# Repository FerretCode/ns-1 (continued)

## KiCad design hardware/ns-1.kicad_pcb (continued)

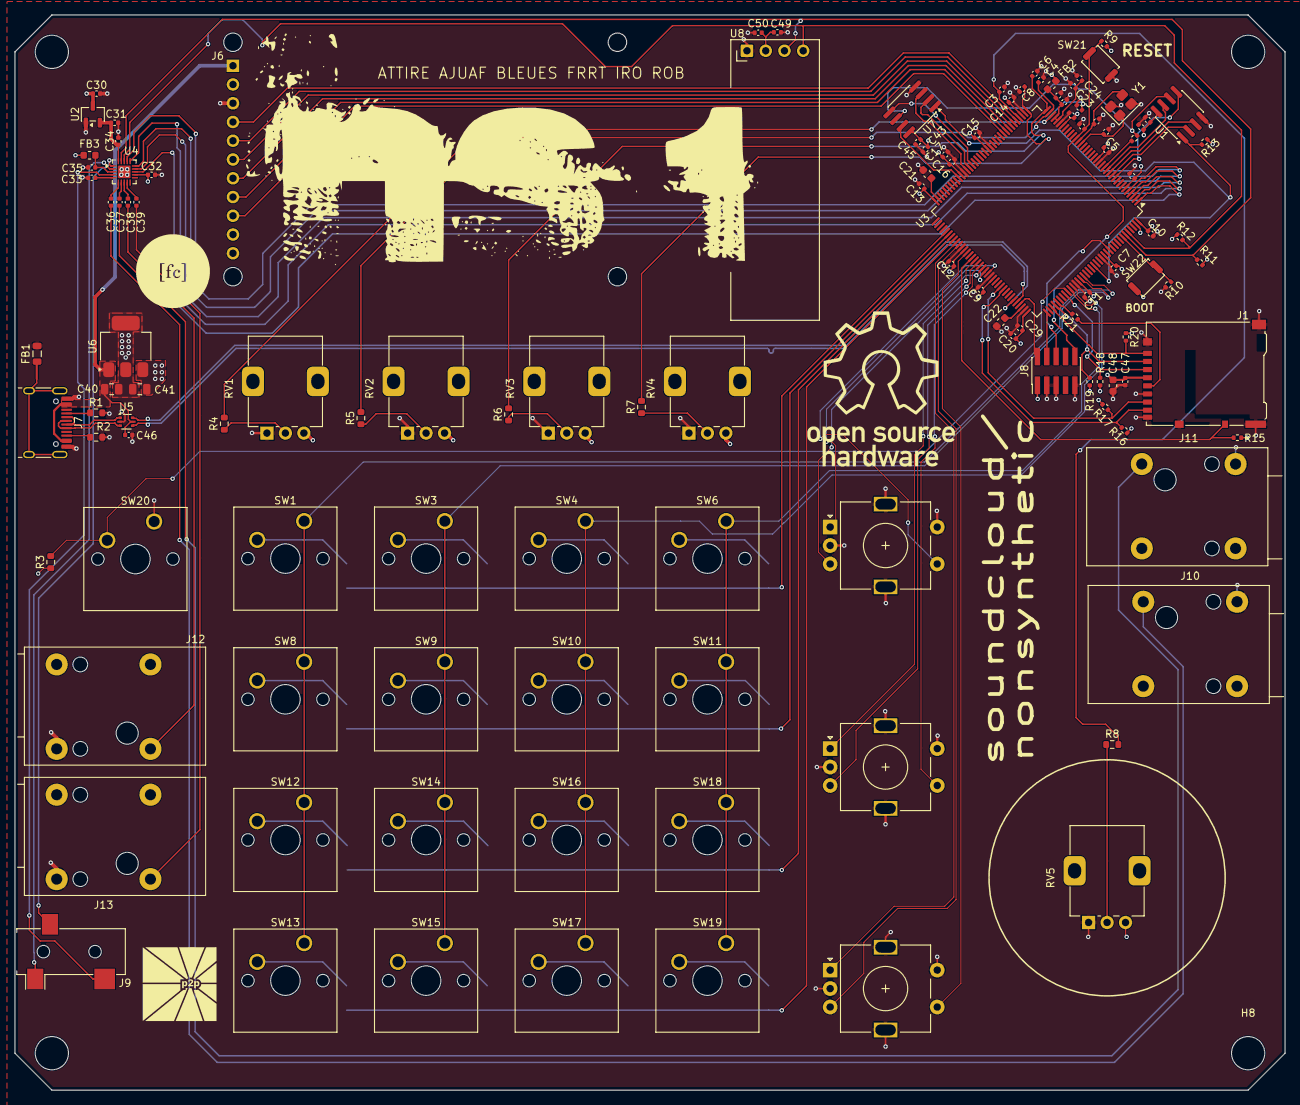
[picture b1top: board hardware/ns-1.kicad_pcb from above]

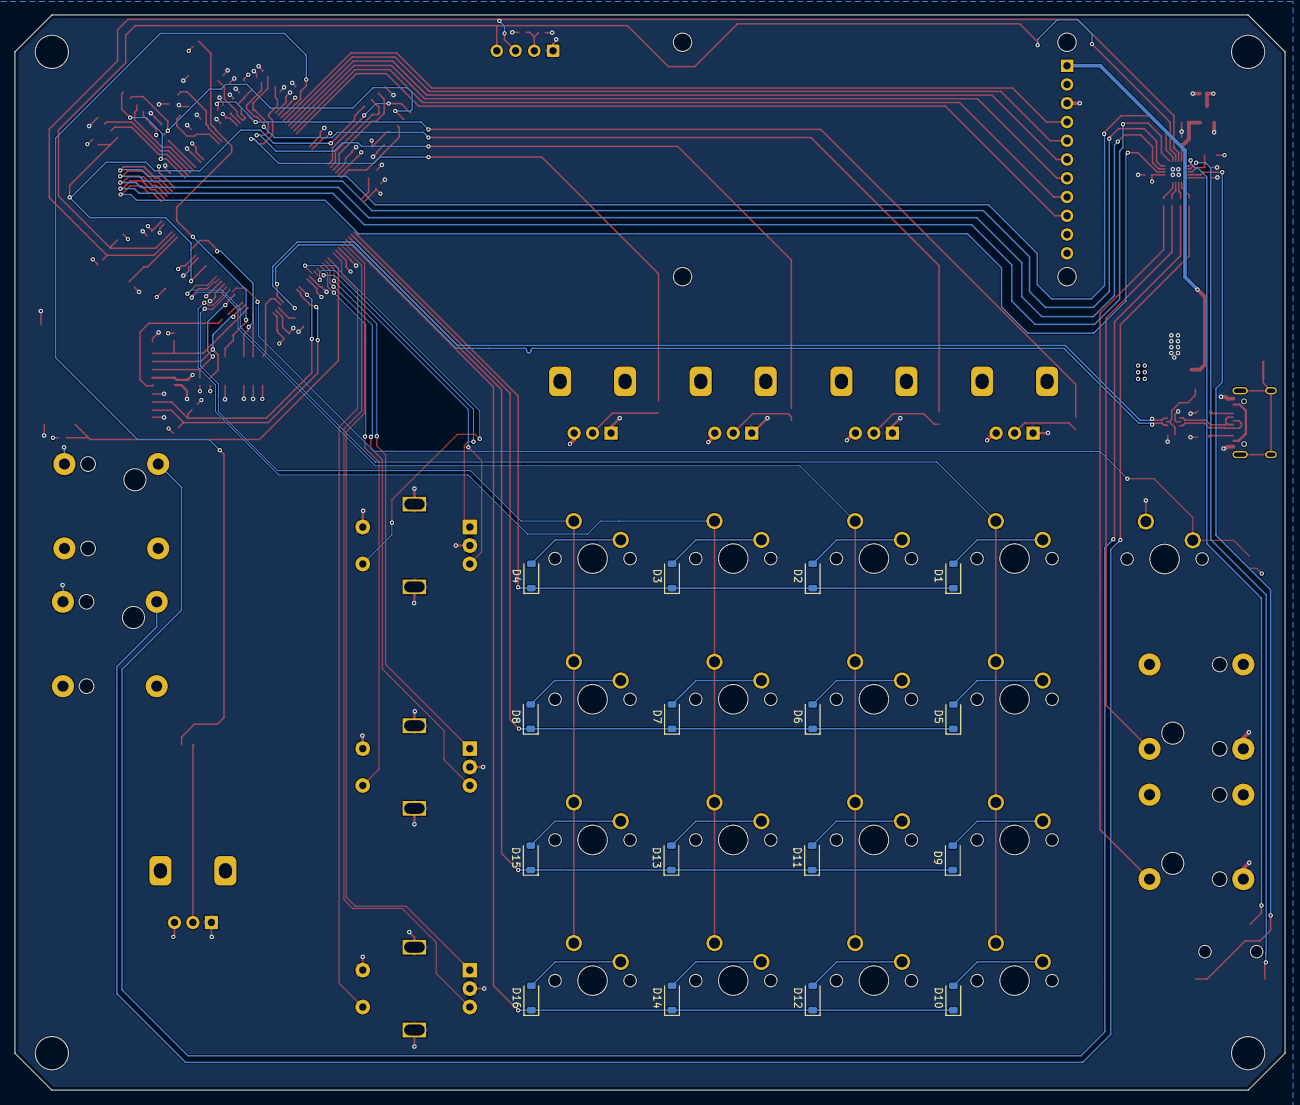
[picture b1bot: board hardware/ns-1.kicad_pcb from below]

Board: 4 copper layers, 172.0 x 145.6 mm, 143 parts (16 on the bottom side), 110 nets.

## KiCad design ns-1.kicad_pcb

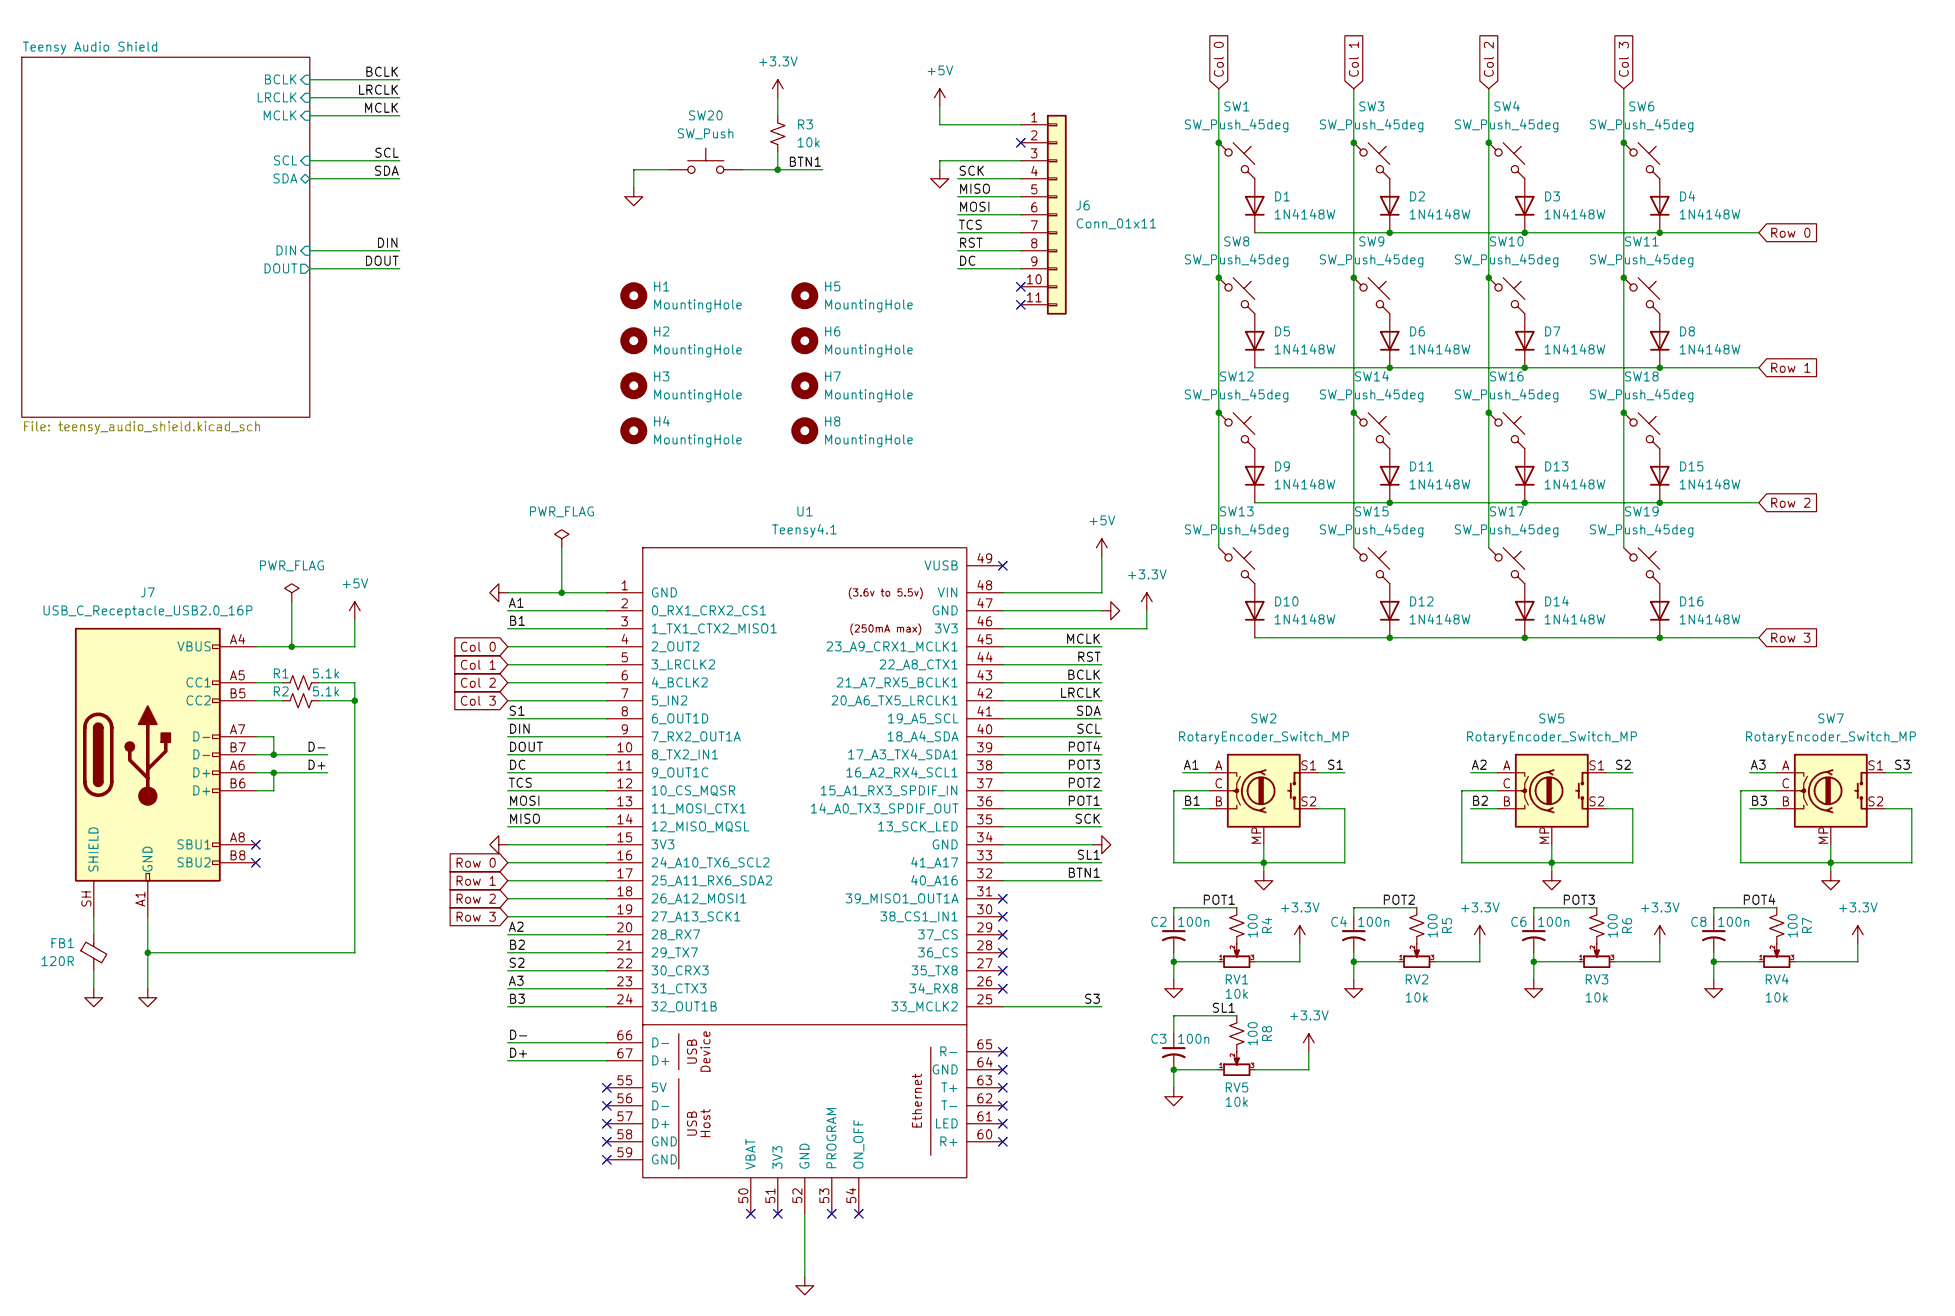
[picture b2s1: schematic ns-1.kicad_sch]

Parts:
C2, C3, C4, C6, C8: 100n; C_0402_1005Metric
D1, D2, D3, D4, D5, D6, D7, D8, D9, D10, D11, D12, D13, D14, D15, D16: 1N4148W; D_SOD-123
FB1: 120R; L_0805_2012Metric
H1, H2, H3, H4: MountingHole; MountingHole_2.5mm
H5, H6, H7, H8: MountingHole; MountingHole_4.5mm
J6: Conn_01x11; PinHeader_1x11_P2.54mm_Vertical
J7: USB_C_Receptacle_USB2.0_16P; USB_C_Receptacle_Amphenol_12401948E412A
R1, R2: 5.1k; R_0603_1608Metric
R3: 10k; R_0603_1608Metric
R4, R5, R6, R7, R8: 100; R_0603_1608Metric
RV1, RV2, RV3, RV4: 10k; Potentiometer_Alps_RK09K_Single_Vertical
RV5: 10k; Potentiometer_Bourns_PTA4543_Single_Slide
SW1, SW3, SW4, SW6, SW8, SW9, SW10, SW11, SW12, SW13, SW14, SW15, SW16, SW17, SW18, SW19: SW_Push_45deg; SW_Cherry_MX_1.00u_PCB
SW2, SW5, SW7: RotaryEncoder_Switch_MP; RotaryEncoder_Alps_EC11E-Switch_Vertical_H20mm
SW20: SW_Push; SW_Cherry_MX_1.00u_PCB
U1: Teensy4.1; Teensy41

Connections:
+3.3V: R3.1, RV1.3, RV2.3, RV3.3, RV4.3, RV5.3, U1.46 (3V3); also elsewhere on the board
+5V: J6.1, J7.A4 (VBUS), J7.A9 (VBUS), J7.B4 (VBUS), J7.B9 (VBUS), U1.48 (VIN)
/A1: SW2.A, U1.2 (0_RX1_CRX2_CS1)
/A2: SW5.A, U1.20 (28_RX7)
/A3: SW7.A, U1.23 (31_CTX3)
/B1: SW2.B, U1.3 (1_TX1_CTX2_MISO1)
/B2: SW5.B, U1.21 (29_TX7)
/B3: SW7.B, U1.24 (32_OUT1B)
/BCLK: U1.43 (21_A7_RX5_BCLK1); also elsewhere on the board
/BTN1: R3.2, SW20.2, U1.32 (40_A16)
/D+: J7.A6 (D+), J7.B6 (D+), U1.67 (D+)
/D-: J7.A7 (D-), J7.B7 (D-), U1.66 (D-)
/DC: J6.9, U1.11 (9_OUT1C)
/DIN: U1.9 (7_RX2_OUT1A); also elsewhere on the board
/DOUT: U1.10 (8_TX2_IN1); also elsewhere on the board
/LRCLK: U1.42 (20_A6_TX5_LRCLK1); also elsewhere on the board
/MCLK: U1.45 (23_A9_CRX1_MCLK1); also elsewhere on the board
/MISO: J6.5, U1.14 (12_MISO_MQSL)
/MOSI: J6.6, U1.13 (11_MOSI_CTX1)
/POT1: C2.1, R4.2, U1.36 (14_A0_TX3_SPDIF_OUT)
/POT2: C4.1, R5.2, U1.37 (15_A1_RX3_SPDIF_IN)
/POT3: C6.1, R6.2, U1.38 (16_A2_RX4_SCL1)
/POT4: C8.1, R7.2, U1.39 (17_A3_TX4_SDA1)
/RST: J6.8, U1.44 (22_A8_CTX1)
/S1: SW2.S1, U1.8 (6_OUT1D)
/S2: SW5.S1, U1.22 (30_CRX3)
/S3: SW7.S1, U1.25 (33_MCLK2)
/SCK: J6.4, U1.35 (13_SCK_LED)
/SCL: U1.40 (18_A4_SDA); also elsewhere on the board
/SDA: U1.41 (19_A5_SCL); also elsewhere on the board
/SL1: C3.1, R8.2, U1.33 (41_A17)
/TCS: J6.7, U1.12 (10_CS_MQSR)
Col 0: SW1.1, SW8.1, SW12.1, SW13.1, U1.4 (2_OUT2)
Col 1: SW3.1, SW9.1, SW14.1, SW15.1, U1.5 (3_LRCLK2)
Col 2: SW4.1, SW10.1, SW16.1, SW17.1, U1.6 (4_BCLK2)
Col 3: SW6.1, SW11.1, SW18.1, SW19.1, U1.7 (5_IN2)
GND: C2.2, C3.2, C4.2, C6.2, C8.2, FB1.2, J6.3, J7.A1 (GND), J7.A12 (GND), J7.B1 (GND), J7.B12 (GND), R1.2, R2.2, RV1.1, RV2.1, RV3.1, RV4.1, RV5.1, SW2.C, SW2.MP, SW2.S2, SW5.C, SW5.MP, SW5.S2, SW7.C, SW7.MP, SW7.S2, SW20.1, U1.1 (GND), U1.15 (3V3), U1.34 (GND), U1.47 (GND), U1.52 (GND); also elsewhere on the board
unnamed: D1.2 (A), SW1.2
unnamed: D2.2 (A), SW3.2
unnamed: D3.2 (A), SW4.2
unnamed: D4.2 (A), SW6.2
unnamed: D5.2 (A), SW8.2
unnamed: D6.2 (A), SW9.2
unnamed: D7.2 (A), SW10.2
unnamed: D8.2 (A), SW11.2
unnamed: D9.2 (A), SW12.2
unnamed: D10.2 (A), SW13.2
unnamed: D11.2 (A), SW14.2
unnamed: D12.2 (A), SW15.2
unnamed: D13.2 (A), SW16.2
unnamed: D14.2 (A), SW17.2
unnamed: D15.2 (A), SW18.2
unnamed: D16.2 (A), SW19.2
unnamed: J7.A5 (CC1), R1.1
unnamed: J7.B5 (CC2), R2.1
unnamed: FB1.1, J7.SH (SHIELD)
unnamed: R4.1, RV1.2
unnamed: R5.1, RV2.2
unnamed: R6.1, RV3.2
unnamed: R7.1, RV4.2
unnamed: R8.1, RV5.2
Row 0: D1.1 (K), D2.1 (K), D3.1 (K), D4.1 (K), U1.16 (24_A10_TX6_SCL2)
Row 1: D5.1 (K), D6.1 (K), D7.1 (K), D8.1 (K), U1.17 (25_A11_RX6_SDA2)
Row 2: D9.1 (K), D11.1 (K), D13.1 (K), D15.1 (K), U1.18 (26_A12_MOSI1)
Row 3: D10.1 (K), D12.1 (K), D14.1 (K), D16.1 (K), U1.19 (27_A13_SCK1)

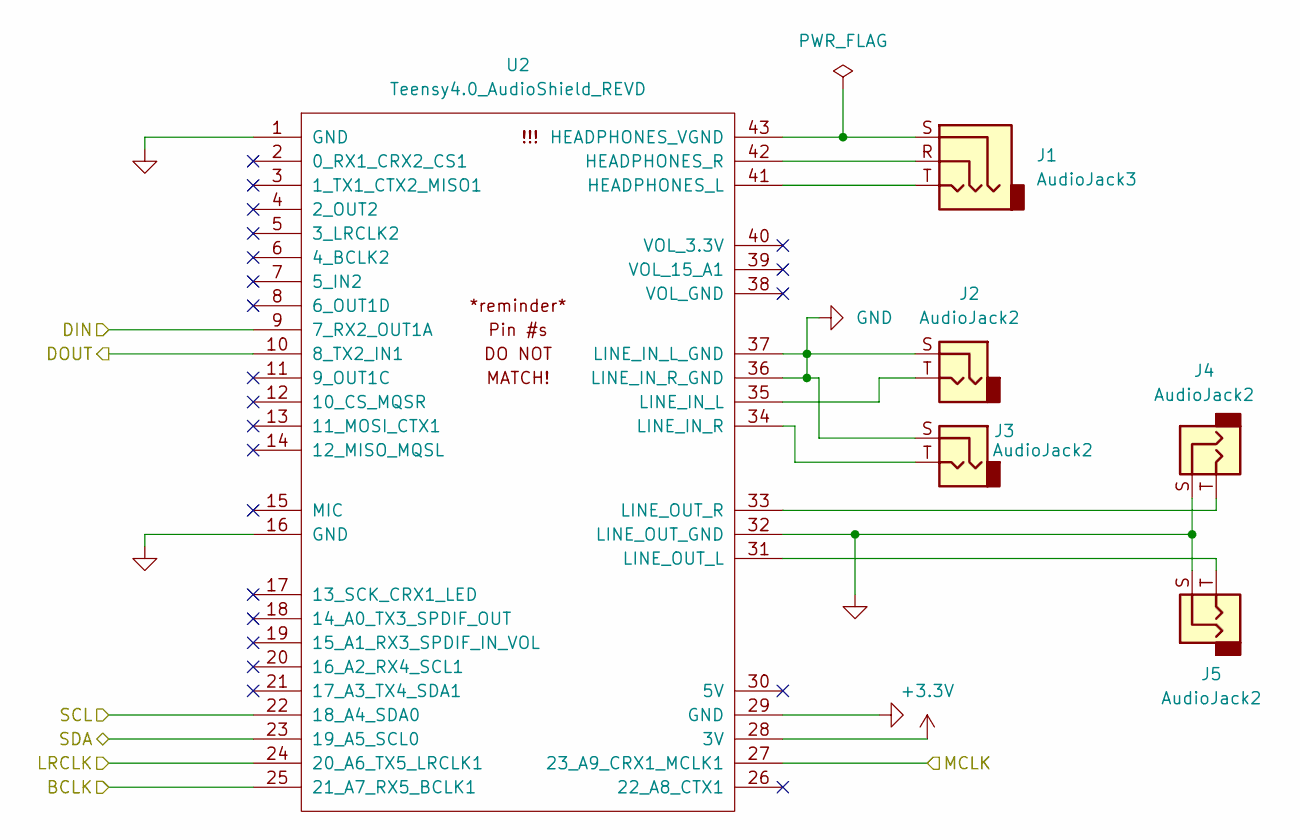
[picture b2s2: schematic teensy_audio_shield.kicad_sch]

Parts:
J1: AudioJack3; Jack_3.5mm_CUI_SJ1-3533NG_Horizontal
J2, J3, J4, J5: AudioJack2; Jack_6.35mm_Neutrik_NRJ4HF_Horizontal
U2: Teensy4.0_AudioShield_REVD; 4.0audioshield

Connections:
+3.3V: U2.28 (3V); also elsewhere on the board
/BCLK: U2.25 (21_A7_RX5_BCLK1); also elsewhere on the board
/DIN: U2.9 (7_RX2_OUT1A); also elsewhere on the board
/DOUT: U2.10 (8_TX2_IN1); also elsewhere on the board
/LRCLK: U2.24 (20_A6_TX5_LRCLK1); also elsewhere on the board
/MCLK: U2.27 (23_A9_CRX1_MCLK1); also elsewhere on the board
/SCL: U2.22 (18_A4_SDA0); also elsewhere on the board
/SDA: U2.23 (19_A5_SCL0); also elsewhere on the board
GND: J2.S, J3.S, J4.S, J5.S, U2.1 (GND), U2.16 (GND), U2.29 (GND), U2.32 (LINE_OUT_GND), U2.36 (LINE_IN_R_GND), U2.37 (LINE_IN_L_GND); also elsewhere on the board
unnamed: J1.T, U2.41 (HEADPHONES_L)
unnamed: J1.R, U2.42 (HEADPHONES_R)
unnamed: J1.S, U2.43 (HEADPHONES_VGND)
unnamed: J2.T, U2.35 (LINE_IN_L)
unnamed: J3.T, U2.34 (LINE_IN_R)
unnamed: J5.T, U2.31 (LINE_OUT_L)
unnamed: J4.T, U2.33 (LINE_OUT_R)

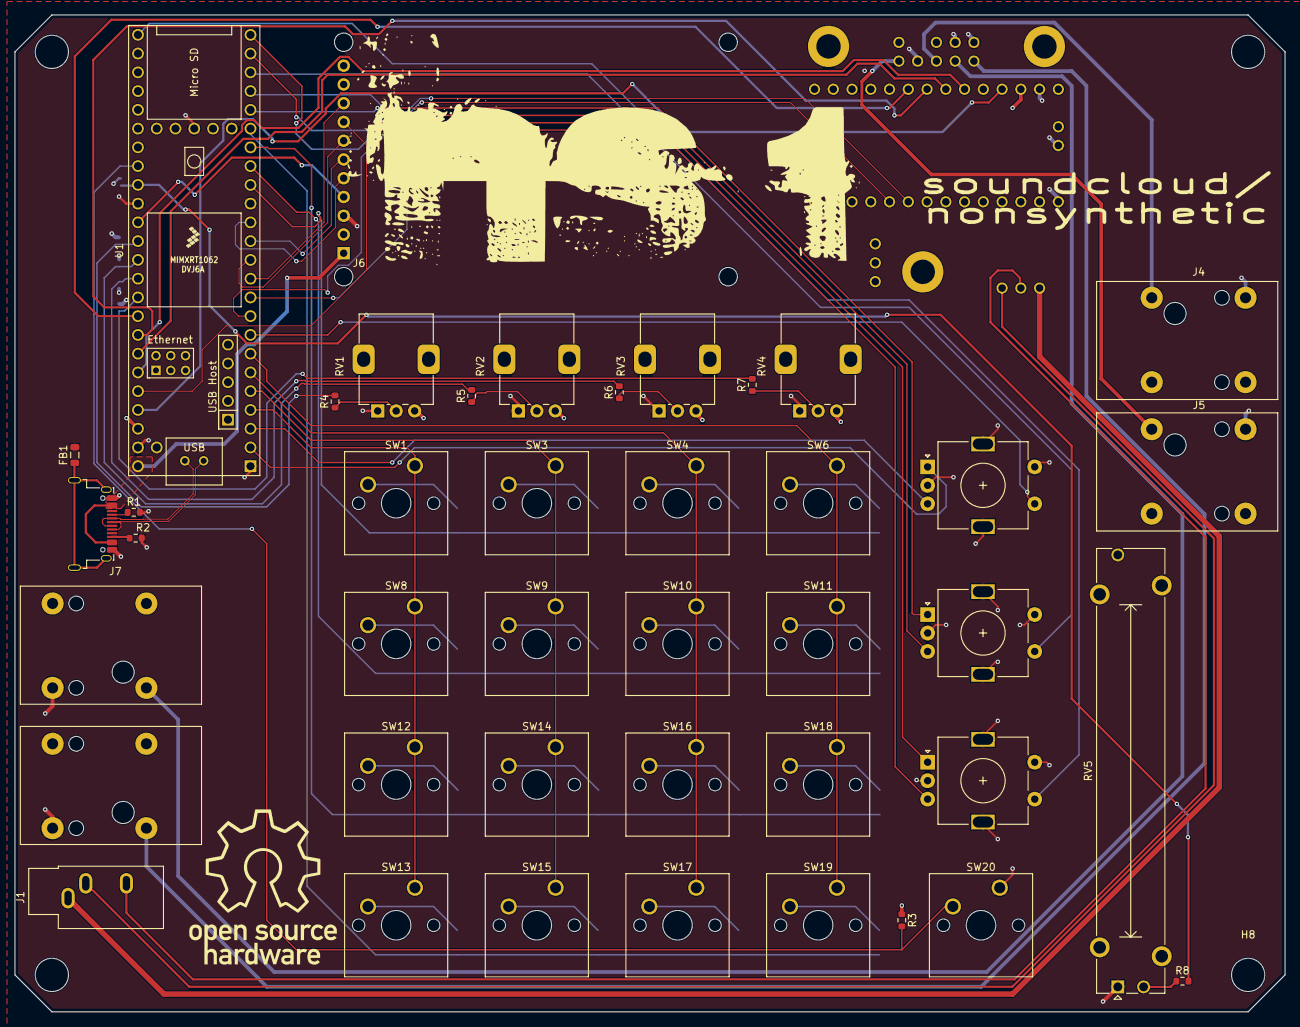
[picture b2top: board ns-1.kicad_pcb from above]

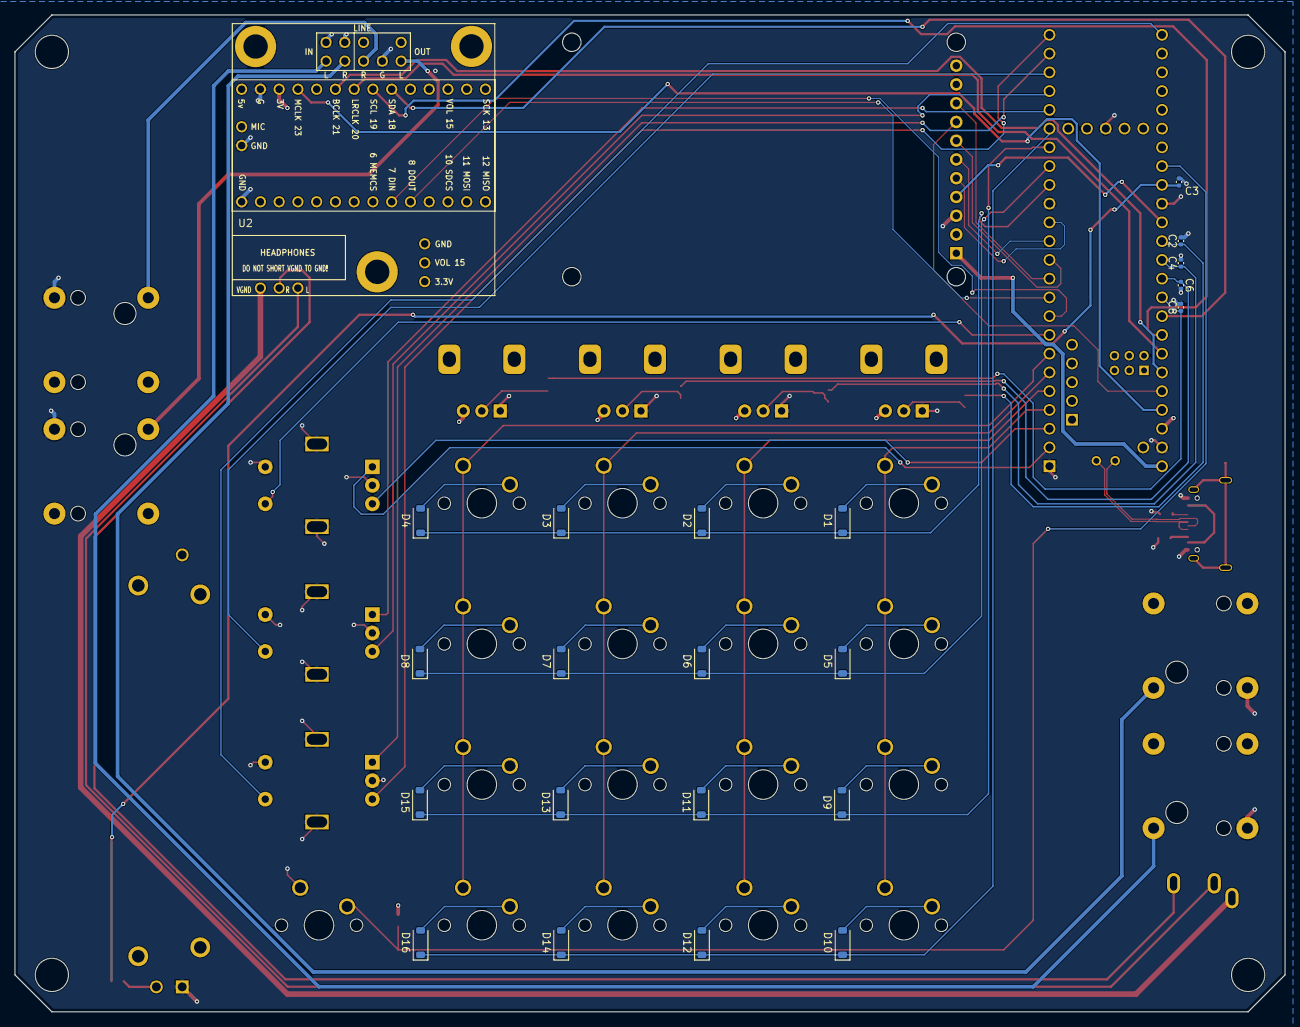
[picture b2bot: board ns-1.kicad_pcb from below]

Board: 4 copper layers, 172.0 x 135.0 mm, 72 parts (22 on the bottom side), 72 nets.

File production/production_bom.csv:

Designator,Footprint,Quantity,Value,LCSC Part #
"C2, C3, C4, C6",0402,4,100n,C22435941
C8,0402,1,100n,
"D1, D10, D11, D12, D13, D14, D15, D16, D2, D3, D4, D5, D6, D7, D8, D9",D_SOD-123,16,1N4148W,C917030
FB1,0805,1,120R,C2943443
J1,Jack_3.5mm_CUI_SJ1-3533NG_Horizontal,1,AudioJack3,
"J2, J3, J4, J5",Jack_6.35mm_Neutrik_NRJ4HF_Horizontal,4,AudioJack2,
J6,PinHeader_1x11_P2.54mm_Vertical,1,Conn_01x11,
J7,USB_C_Receptacle_HRO_TYPE-C-31-M-12,1,USB_C_Receptacle_USB2.0_16P,C3197899
"R1, R2",0603,2,5.1k,C2906874
R3,0603,1,10k,C317926
"R4, R5, R6, R7, R8",0603,5,100,C122970
"RV1, RV2, RV3, RV4",Potentiometer_Alps_RK09K_Single_Vertical,4,10k,
RV5,Potentiometer_Bourns_PTA4543_Single_Slide,1,10k,
"SW1, SW10, SW11, SW12, SW13, SW14, SW15, SW16, SW17, SW18, SW19, SW3, SW4, SW6, SW8, SW9",SW_Cherry_MX_1.00u_PCB,16,SW_Push_45deg,
"SW2, SW5, SW7",RotaryEncoder_Alps_EC11E-Switch_Vertical_H20mm,3,RotaryEncoder_Switch_MP,
SW20,SW_Cherry_MX_1.00u_PCB,1,SW_Push,
U1,Teensy41,1,Teensy4.1,
U2,4.0audioshield,1,Teensy4.0_AudioShield_REVD,

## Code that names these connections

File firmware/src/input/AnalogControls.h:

#pragma once

#include "../config/Config.h"
#include "../config/Pins.h"
#include <Arduino.h>

class AnalogControls {
  public:
    void begin();
    void update();

    float pot(uint8_t index) const {
        return potSmoothed[index];
    } // 0..3, normalized 0..1

    float slider() const { return sliderSmoothed; } // normalized 0..1

    bool shiftDown() const { return shiftState; }
    bool shiftJustPressed();
    bool shiftJustReleased();

  private:
    const uint8_t potPins[4] = {PIN_POT1, PIN_POT2, PIN_POT3, PIN_POT4};
    float potSmoothed[4] = {0.0f, 0.0f, 0.0f, 0.0f};
    float sliderSmoothed = 0.0f;

    bool shiftState = false;
    bool shiftPendingPress = false;
    bool shiftPendingRelease = false;
    uint32_t shiftLastChangeMicros = 0;
};

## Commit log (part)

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2026-06-26 add first board revision
